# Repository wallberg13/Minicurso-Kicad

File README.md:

# Construção de Layout de Placas de Circuito Impresso (PCBs) utilizando KiCad - Semana Acadêmica de Engenharia de Computação

Repositório com objetivo de deixar guardado todo o conteúdo ministrado nesse
mini-curso a fim de ser disponível para todos.

## Objetivos desse mini-curso

### Objetivo Geral
- Saber elaborar uma PCB com malha de terra.

### Objetivos Específico
- Saber fazer o esquemático de um circuito.
- Conhecer os atalhos básicos do KiCad.
- Aprender fazer roteamento de uma PCB a partir de um esquemático.
- Utilizar padrões de projeto de PCBs fazendo o uso de boas práticas.

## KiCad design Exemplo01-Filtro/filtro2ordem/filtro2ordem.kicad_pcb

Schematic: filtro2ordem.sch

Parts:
C1, C2: C; C_Disc_D10.5mm_W5.0mm_P7.50mm
J1, J2: Conn_01x02; TerminalBlock_bornier-2_P5.08mm
J3: Conn_01x03; TerminalBlock_bornier-3_P5.08mm
R1, R2: R; R_Axial_DIN0414_L11.9mm_D4.5mm_P15.24mm_Horizontal
U1: TL084; DIP-14_W7.62mm_Socket_LongPads

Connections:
GND: C2.2, J1.2, J2.2, J3.3
unnamed: C1.2, R1.1, R2.2
unnamed: C2.1, R2.1, U1.3 (+)
V+: J3.1, U1.4 (V+)
V-: J3.2, U1.11 (V-)
Vin: J1.1, R1.2
Vout: C1.1, J2.1, U1.1, U1.2 (-)

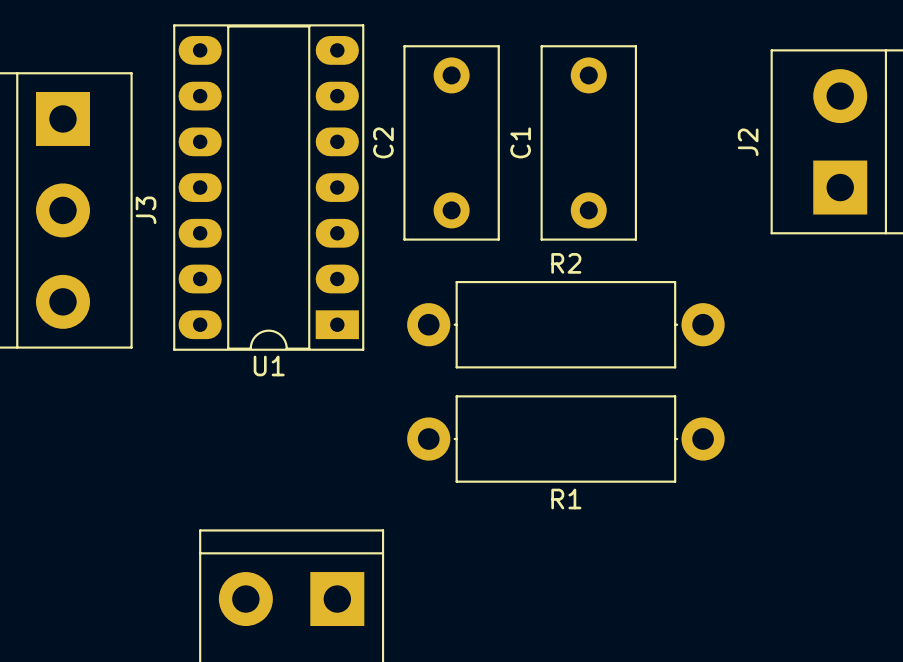
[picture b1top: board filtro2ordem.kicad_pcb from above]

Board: 2 copper layers, 8 parts (0 on the bottom side), 7 nets.

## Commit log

2018-08-11 Primeiro Commit
2018-08-12 Adicionado primeira aula de instalação do Kicad. A primeira aula se destina ao download dos arquivos de instalação de como é feita em 3 sistemas operacionais diferentes.
    Adicionado um exemplo de pcb, que será feita durante as aulas do minicurso.
    Essa pcb trata-se de um filtro de segunda ordem. Nos slides, se houver mais de
    um, será utilizado como exemplo nos prints esse circuito.
    Aula01 e circuito incompletos.
2018-08-12 Aprimorando o README
2018-08-12 Create LICENSE
2018-08-12 Finalização do minitutorial de instalação do Kicad
2018-08-17 Adicionando o exemplo que será usado em sala
2018-08-17 Atualizando nome do mini-curso
2018-08-20 Adicionando Aula 02 do minicurso.
2018-09-02 Ultimas alteracoes
